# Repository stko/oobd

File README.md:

# OOBD - The Open Onboard Diagnostics Toolkit

OOBD (Open On Board Diagnostics) is a collection of open Source software and hardware for OBD Vehicle Diagnostics. Our target is to provide a flexible platform to do the most diagnostic tasks quick, handy and reliable. To do so, we've developed a whole set of applications, hardware and tools - and we still continue..

# Quickstart

To download, install, setup and run the software, please follow the instructions for [Android](http://oobd.org/doku.php?id=doc:startup_android) or [Windows](http://oobd.org/doku.php?id=doc:startup_windows).

For all documents, please use the links [Sitemap](http://oobd.org/doku.php?id=start&do=index) and [Manual](http://oobd.org/doku.php?id=doc:start) provided in the header of each page.

# Features
As the feature list became to long for the main page, we moved it to the separate [Feature](http://oobd.org/doku.php?id=web:features) page.

# Hardware

Although the build plans are available in the OOBD repository, we do recommend to better buy a finished CAN invader device at our partner [JATRA](http://caninvader.com/). It was found that there's a lot of experience and time needed to collect all parts and to solder the dongle by yourself. Especially for commercial applications it's more effective to directly order the complete units.

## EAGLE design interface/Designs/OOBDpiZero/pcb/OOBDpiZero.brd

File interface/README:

The OOBD firmware directory structure

The OOBD firmware has several hardware realisations (Designs), but always a common software core. To handle them all in one repository,
they are seperated into different Design Folders

`-- Designs
    |-- CORTEX
    |   `-- STM32F103E_Eclipse_GCC
    |       `-- D2
    `-- POSIX
        `-- GCC
            `-- D3

first sorted by the microcontroller platform, then by its particular controller itself and finally by the hardware design (Dxx), on which
that controller is used on.

The designs contains both the hardware description files (Schematics, PCB, etc) and also the software abstraction layers,
which connects the abstract functions to the real hardware and do also all the low level data handling like e.g.  the CAN -Bus

To make it simple, these designs just get a different number. Actual we have:

D1: the first, never realized protoype with an Atmel controller
D2: DXM hardware, optional combined with our own bus switching unit
D3: A pure simulator environment, emulating FreeRTOS and OOBD firmware as normal Unix pogramm. paired with a virtual serial port and a CAN-Bus
    simulator, written in python

The OOBD firmware core is hardware independend and so not bounded to the design folders.

It can be found in the OOBD folder, followed by a version folder for later extensions

`-- OOBD
    `-- v1

Finally the OS itself (we are using FreeRTOS) has is own indepenting directory structure, alligned to the standard structure of the FreeRTOS project.

`-- OS
    `-- FreeRTOSV6.1.0
        |-- Demo
        |   |-- Common
        |-- License
        `-- Source
            |-- include
            `-- portable

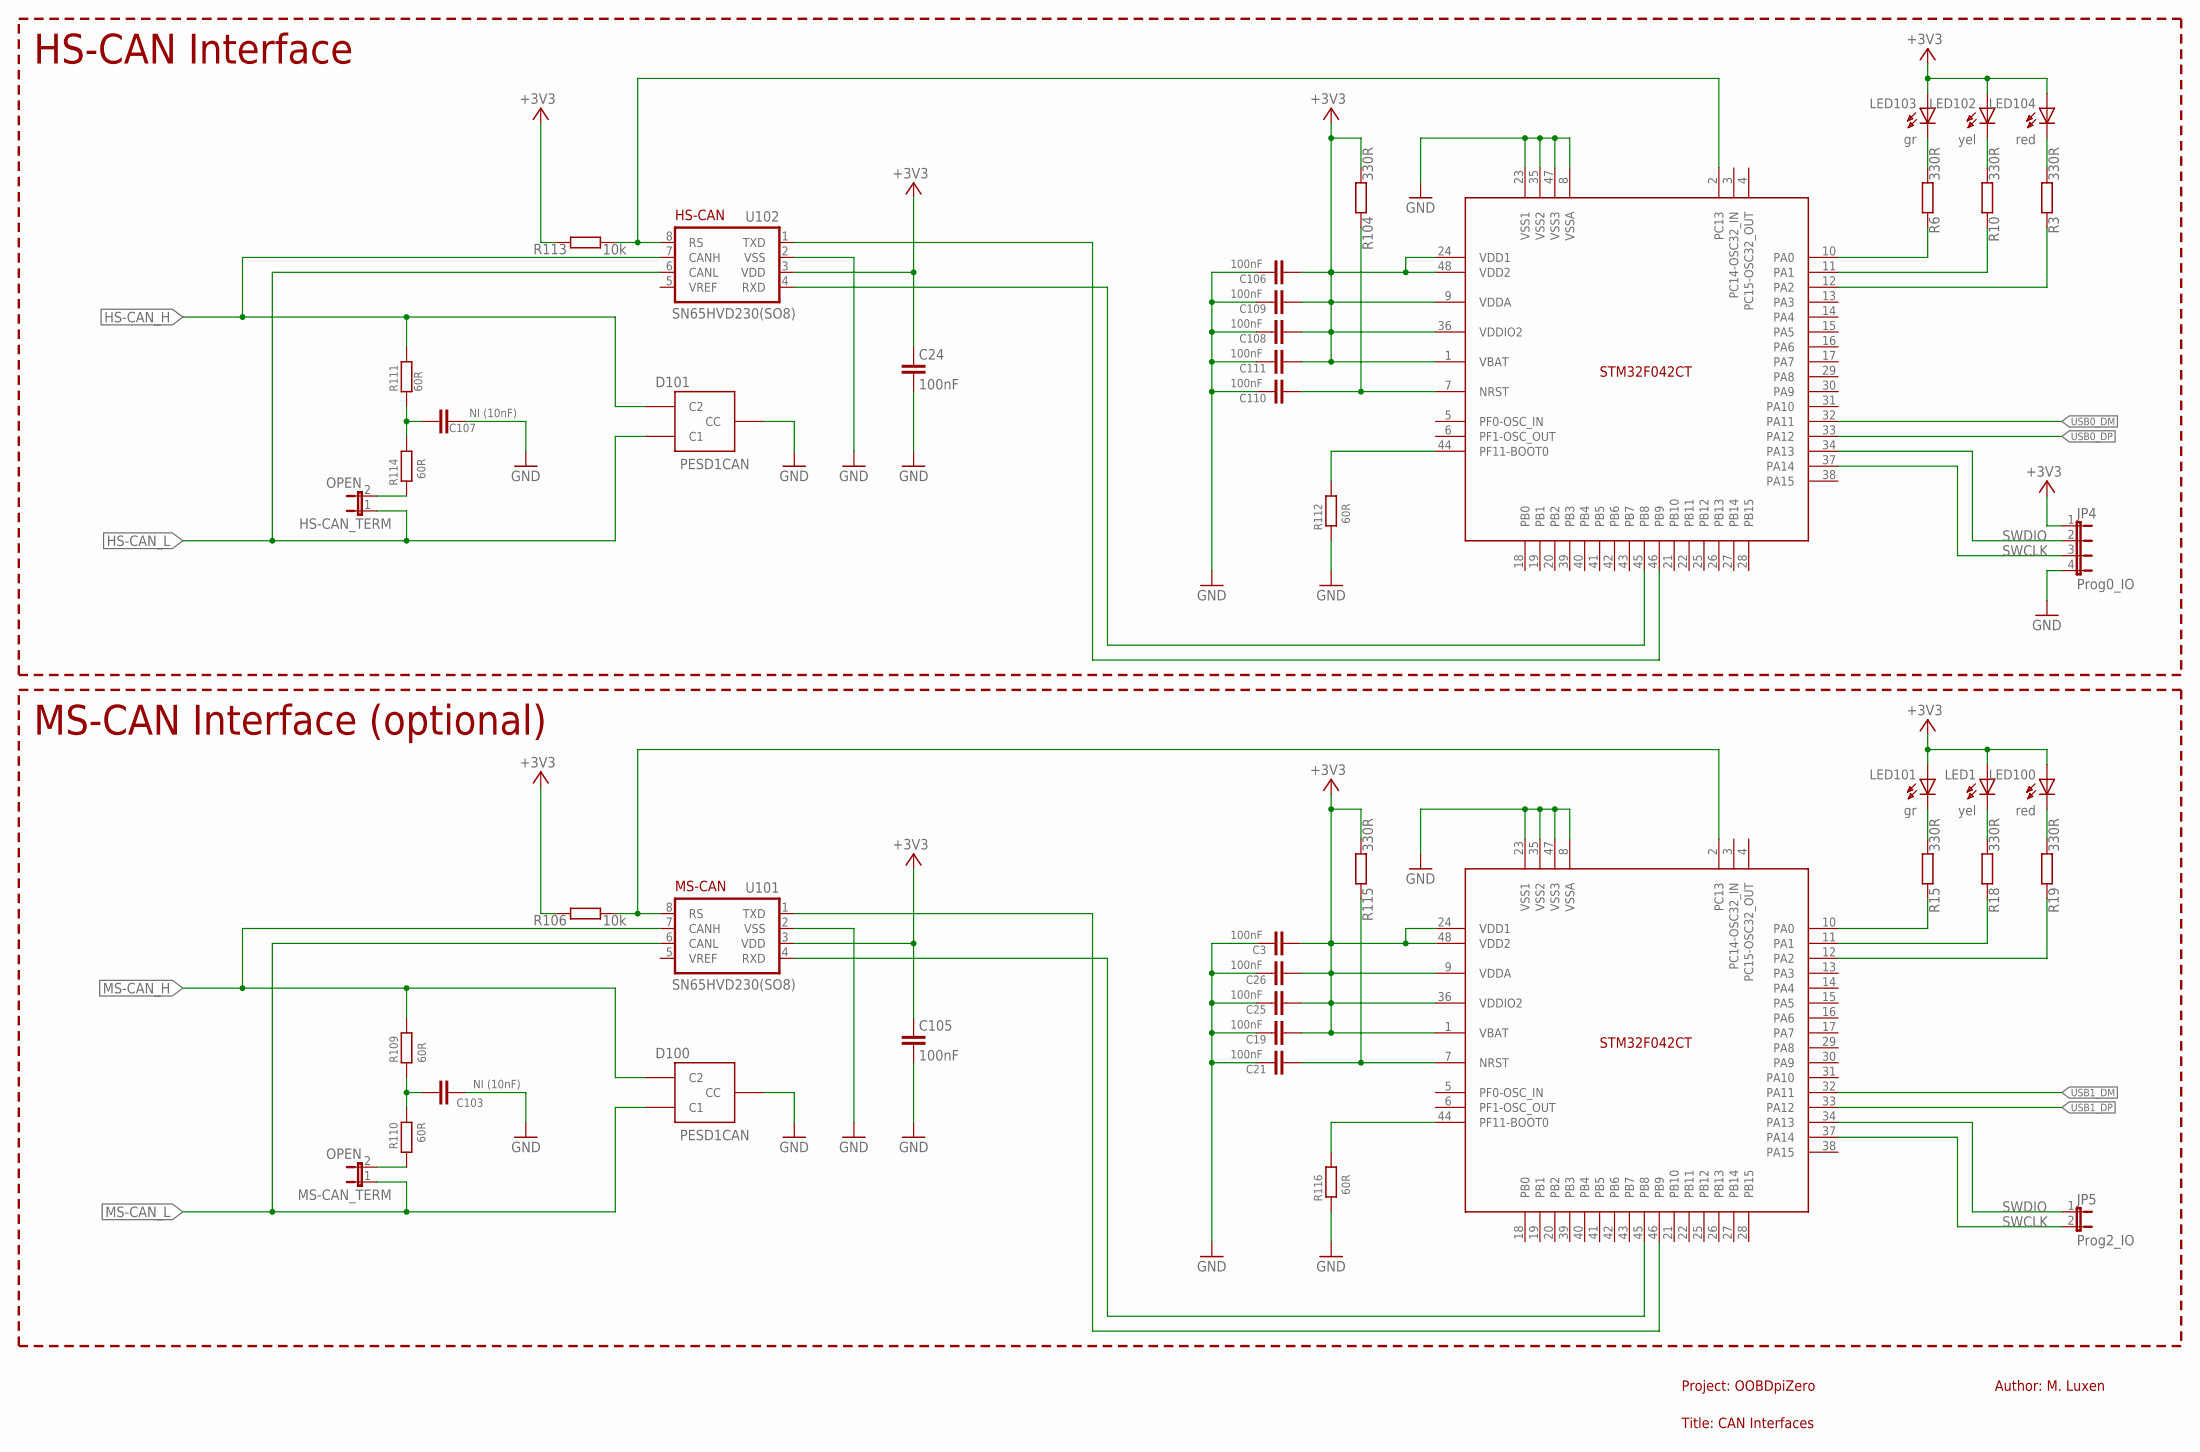
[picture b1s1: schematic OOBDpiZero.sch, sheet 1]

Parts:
C3, C19, C21, C25, C26, C106, C108, C109, C110, C111: 100nF; C0603
C24, C105: 100nF; C0603K
C103, C107: NI (10nF); C0603
D100, D101: PESD1CAN; SOT23
HS-CAN_TERM: OPEN; 1X02
JP4: Prog0_IO; JP4
JP5: Prog2_IO; JP1
LED1, LED102: yel; LED_0603
LED100, LED104: red; LED_0603
LED101, LED103: gr; LED_0603
MS-CAN_TERM: OPEN; 1X02
R3, R6, R10, R15, R18, R19, R104, R115: 330R; R0603
R106, R113: 10k; R0603
R109, R110, R111, R112, R114, R116: 60R; R0603
U101, U102: SN65HVD230(SO8); SO-08
U$100, U$102: STM32F042CT; LQFP48

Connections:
+3V3: C3.2, C19.2, C24.1, C25.2, C26.2, C105.1, C106.2, C108.2, C109.2, C111.2, JP4.1, LED1.A, LED100.A, LED101.A, LED102.A, LED103.A, LED104.A, R104.1, R106.2, R113.2, R115.1, U101.3 (VDD), U102.3 (VDD), U$100.1 (VBAT), U$100.9 (VDDA), U$100.24 (VDD1), U$100.36 (VDDIO2), U$100.48 (VDD2), U$102.1 (VBAT), U$102.9 (VDDA), U$102.24 (VDD1), U$102.36 (VDDIO2), U$102.48 (VDD2); also elsewhere on the board
GND: C3.1, C19.1, C21.1, C24.2, C25.1, C26.1, C103.2, C105.2, C106.1, C107.2, C108.1, C109.1, C110.1, C111.1, D100.3 (CC), D101.3 (CC), JP4.4, R112.2, R116.2, U101.2 (VSS), U102.2 (VSS), U$100.8 (VSSA), U$100.23 (VSS1), U$100.35 (VSS2), U$100.47 (VSS3), U$102.8 (VSSA), U$102.23 (VSS1), U$102.35 (VSS2), U$102.47 (VSS3); also elsewhere on the board
HS-CAN_H: D101.2 (C2), R111.2, U102.7 (CANH); also elsewhere on the board
HS-CAN_L: D101.1 (C1), HS-CAN_TERM.1, U102.6 (CANL); also elsewhere on the board
HS-CAN_RXD: U102.4 (RXD), U$100.45 (PB8)
HS-CAN_TXD: U102.1 (TXD), U$100.46 (PB9)
MS-CAN_H: D100.2 (C2), R109.2, U101.7 (CANH); also elsewhere on the board
MS-CAN_L: D100.1 (C1), MS-CAN_TERM.1, U101.6 (CANL); also elsewhere on the board
MS-CAN_RXD: U101.4 (RXD), U$102.45 (PB8)
MS-CAN_TXD: U101.1 (TXD), U$102.46 (PB9)
unnamed: C107.1, R111.1, R114.1
unnamed: R113.1, U102.8 (RS), U$100.2 (PC13)
unnamed: C103.1, R109.1, R110.1
unnamed: R6.2, U$100.10 (PA0)
unnamed: R10.2, U$100.11 (PA1)
unnamed: R112.1, U$100.44 (PF11-BOOT0)
unnamed: R3.2, U$100.12 (PA2)
unnamed: LED104.C, R3.1
unnamed: LED102.C, R10.1
unnamed: LED103.C, R6.1
unnamed: C110.2, R104.2, U$100.7 (NRST)
unnamed: R116.1, U$102.44 (PF11-BOOT0)
unnamed: R15.2, U$102.10 (PA0)
unnamed: R18.2, U$102.11 (PA1)
unnamed: R19.2, U$102.12 (PA2)
unnamed: LED100.C, R19.1
unnamed: LED1.C, R18.1
unnamed: LED101.C, R15.1
unnamed: C21.2, R115.2, U$102.7 (NRST)
unnamed: HS-CAN_TERM.2, R114.2
unnamed: MS-CAN_TERM.2, R110.2
unnamed: R106.1, U101.8 (RS), U$102.2 (PC13)
SWCLK: JP4.3, JP5.2, U$100.37 (PA14), U$102.37 (PA14)
SWDIO: JP4.2, JP5.1, U$100.34 (PA13), U$102.34 (PA13)
USB0_DM: U$100.32 (PA11); also elsewhere on the board
USB0_DP: U$100.33 (PA12); also elsewhere on the board
USB1_DM: U$102.32 (PA11); also elsewhere on the board
USB1_DP: U$102.33 (PA12); also elsewhere on the board

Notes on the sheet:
HS-CAN Interface
Project: OOBDpiZero
Title: CAN Interfaces
HS-CAN
MS-CAN Interface (optional)
MS-CAN
Author: M. Luxen

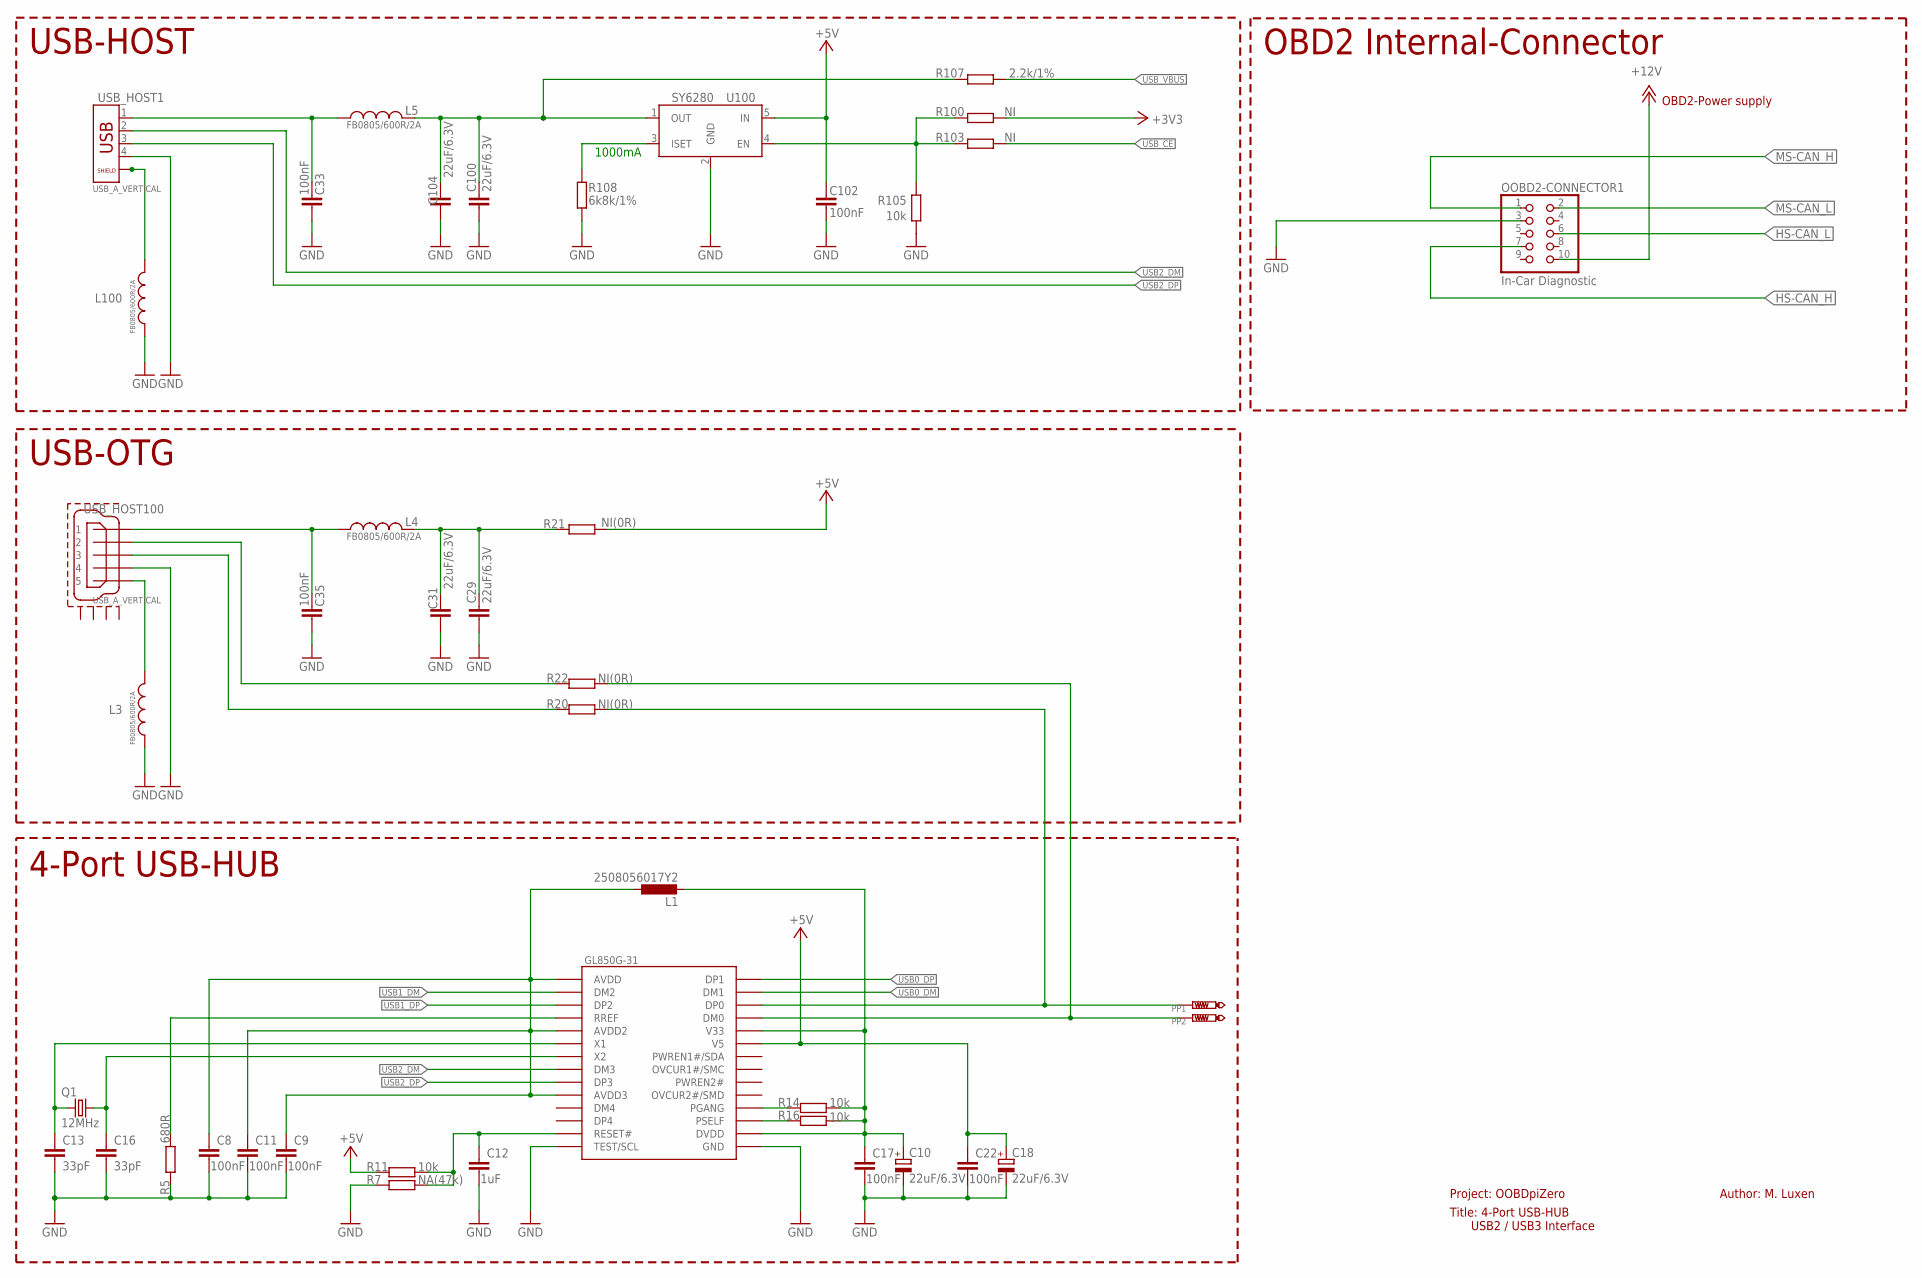
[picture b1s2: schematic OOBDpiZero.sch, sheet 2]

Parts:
C8, C9, C11, C17, C22: 100nF; C0603
C10, C18: 22uF/6.3V; SMC_A
C12: 1uF; C0603
C13, C16: 33pF; C0603
C29, C31, C100, C104: 22uF/6.3V; C0603
C33, C35, C102: 100nF; C0603K
L1: 2508056017Y2; L0805@1
L3, L4, L5, L100: FB0805/600R/2A; L0603
OOBD2-CONNECTOR1: In-Car Diagnostic; 2X05/90
PP1, PP2: PTR1PAD1-11; P1-11
Q1: 12MHz; SM49
R5: 680R; R0603
R7: NA(47k); R0603
R11, R14, R16, R105: 10k; R0603
R20, R22: NI(0R); R0603
R21: NI(0R); R0805
R100, R103: NI; R0603
R107: 2.2k/1%; R0603
R108: 6k8k/1%; R0603
U100: SY6280; SOT23-5
U$101: GL850G-31; TSSOP28
USB_HOST1: USB_A_VERTICAL; USB_PN87520_DEV_PTH
USB_HOST100: USB_A_VERTICAL; 47589-0001

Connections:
+3V3: R100.2; also elsewhere on the board
+5V: C18.+, C22.1, C102.1, R11.1, R21.2, U100.5 (IN), U$101.23 (V5); also elsewhere on the board
+12V: OOBD2-CONNECTOR1.10; also elsewhere on the board
GND: C8.2, C9.2, C10.-, C11.2, C12.2, C13.2, C16.2, C17.2, C18.-, C22.2, C29.2, C31.2, C33.2, C35.2, C100.2, C102.2, C104.2, L3.1, L100.1, OOBD2-CONNECTOR1.3, R5.1, R7.1, R105.1, R108.1, U100.2 (GND), U$101.14 (TEST/SCL), U$101.15 (GND), USB_HOST1.4, USB_HOST100.4; also elsewhere on the board
HS-CAN_H: OOBD2-CONNECTOR1.7; also elsewhere on the board
HS-CAN_L: OOBD2-CONNECTOR1.6; also elsewhere on the board
MS-CAN_H: OOBD2-CONNECTOR1.1; also elsewhere on the board
MS-CAN_L: OOBD2-CONNECTOR1.2; also elsewhere on the board
unnamed: C29.1, C31.1, L4.1, R21.1
unnamed: C16.1, Q1.2, U$101.7 (X2)
unnamed: C13.1, Q1.1, U$101.6 (X1)
unnamed: C10.+, C17.1, L1.2, R14.2, R16.2, U$101.16 (DVDD), U$101.24 (V33)
unnamed: R14.1, U$101.18 (PGANG)
unnamed: R16.1, U$101.17 (PSELF)
unnamed: C12.1, R7.2, R11.2, U$101.13 (RESET#)
unnamed: R22.1, USB_HOST100.2
unnamed: C8.1, C9.1, C11.1, L1.1, U$101.1 (AVDD), U$101.5 (AVDD2), U$101.10 (AVDD3)
unnamed: R5.2, U$101.4 (RREF)
unnamed: C33.1, L5.2, USB_HOST1.1
unnamed: L100.2, USB_HOST1.P$1 (5), USB_HOST1.P$2 (6)
unnamed: R20.1, USB_HOST100.3
unnamed: L3.2, USB_HOST100.5
unnamed: R108.2, U100.3 (ISET)
unnamed: C100.1, C104.1, L5.1, R107.2, U100.1 (OUT)
unnamed: C35.1, L4.2, USB_HOST100.1
PP22: PP1.P$1, R20.2, U$101.26 (DP0)
PP23: PP2.P$1, R22.2, U$101.25 (DM0)
USB0_DM: U$101.27 (DM1); also elsewhere on the board
USB0_DP: U$101.28 (DP1); also elsewhere on the board
USB1_DM: U$101.2 (DM2); also elsewhere on the board
USB1_DP: U$101.3 (DP2); also elsewhere on the board
USB1_EN: R100.1, R103.1, R105.2, U100.4 (EN)
USB2_DM: U$101.8 (DM3), USB_HOST1.2
USB2_DP: U$101.9 (DP3), USB_HOST1.3
USB_CE: R103.2; also elsewhere on the board
USB_VBUS: R107.1; also elsewhere on the board

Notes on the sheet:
USB-HOST
1000mA
USB-OTG
4-Port USB-HUB
Project: OOBDpiZero
Title: 4-Port USB-HUB USB2 / USB3 Interface
Author: M. Luxen
OBD2-Power supply
OBD2 Internal-Connector

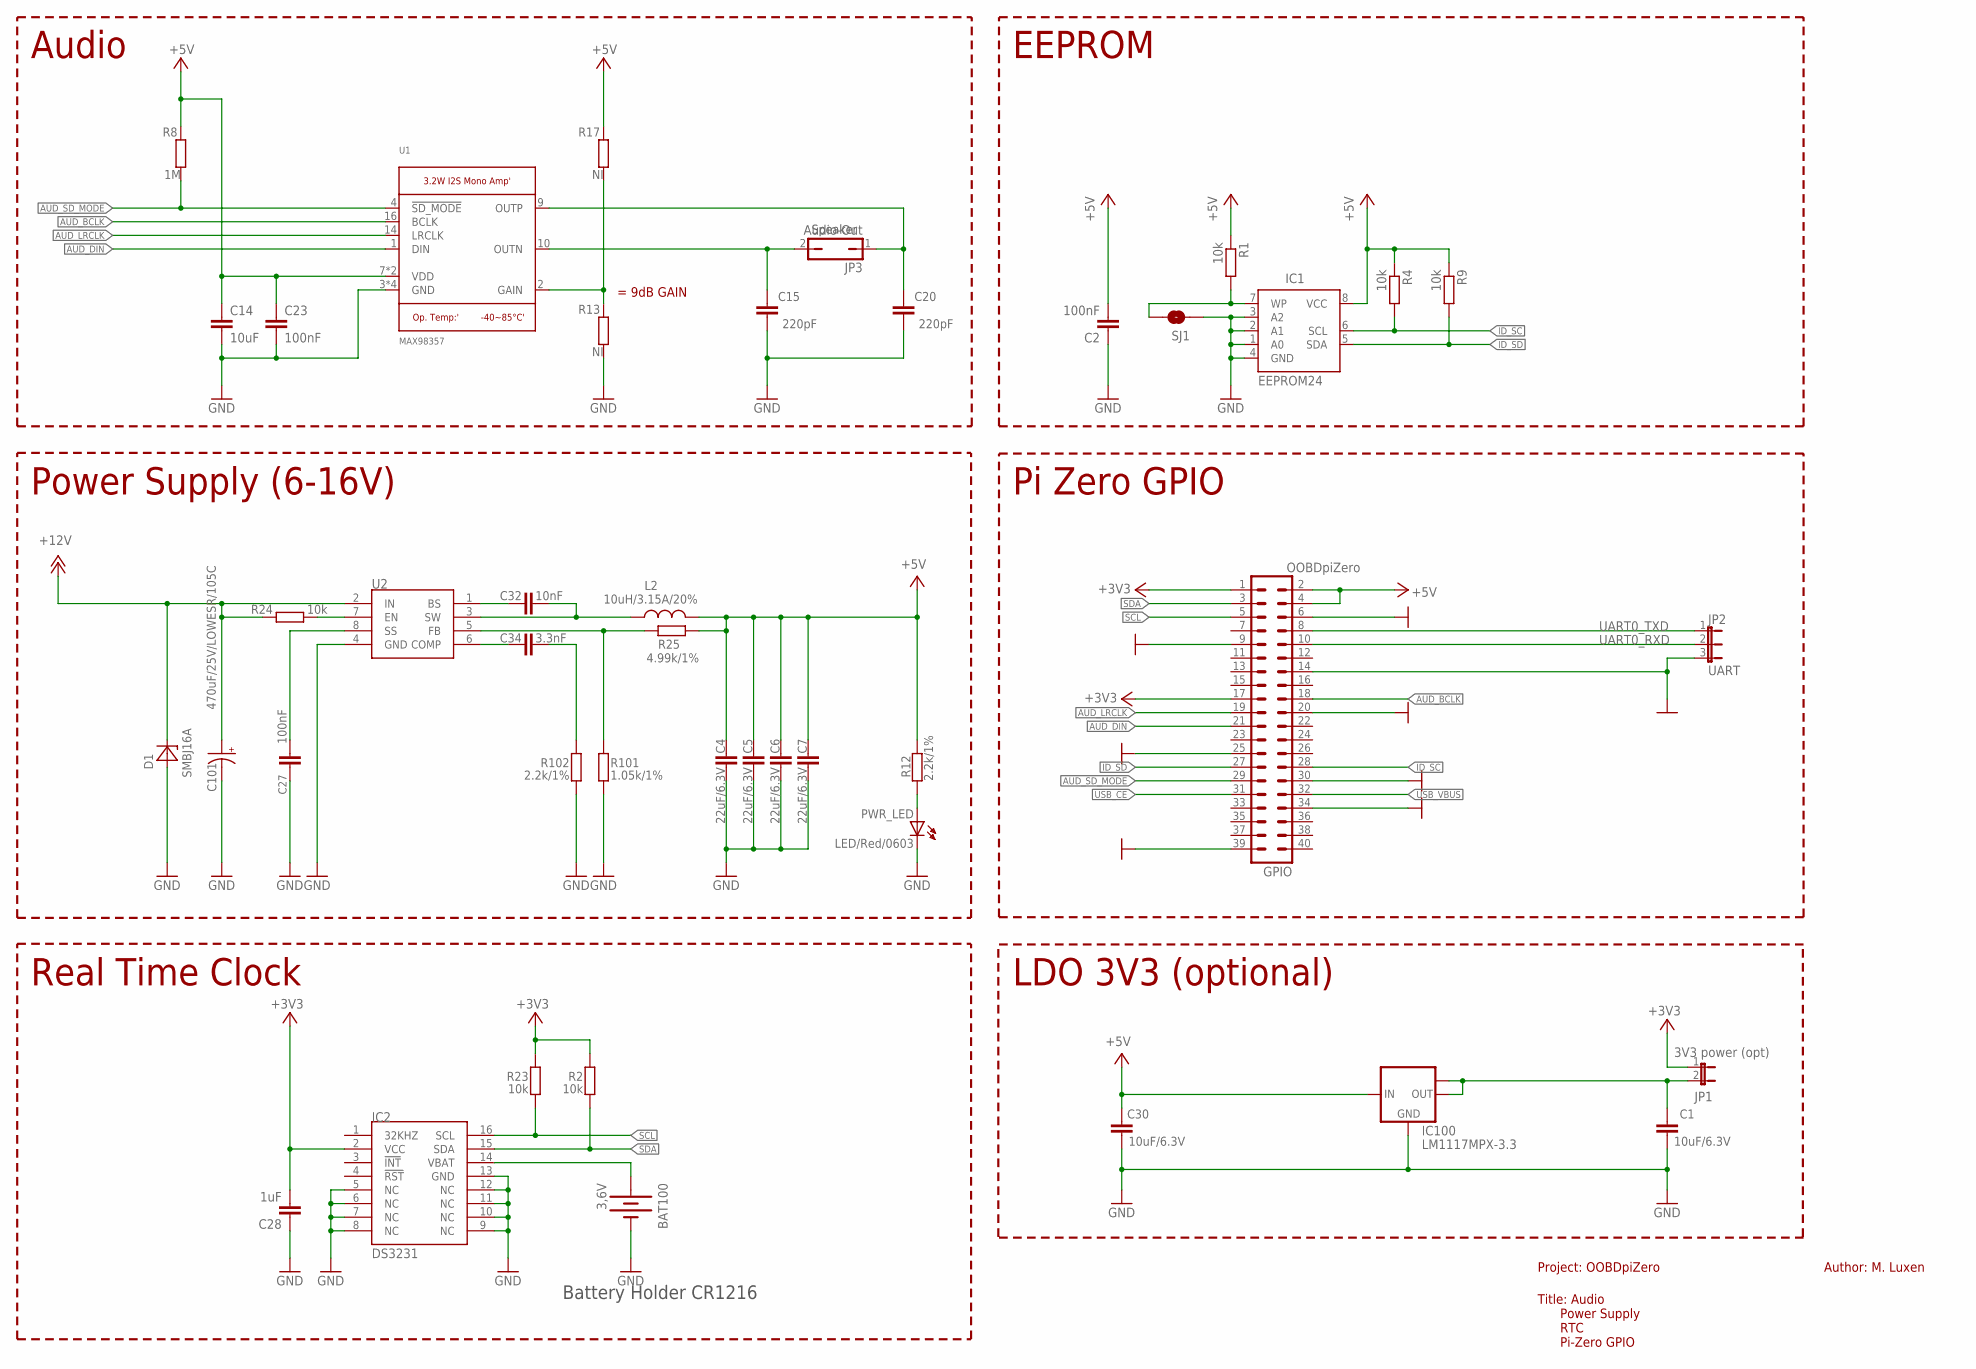
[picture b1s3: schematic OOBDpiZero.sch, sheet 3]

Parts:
BAT100: 3,6V; BATTCON_12MM_PTH
C1, C30: 10uF/6.3V; C0603
C2, C27: 100nF; C0603
C4, C5, C6, C7: 22uF/6.3V; C0603
C14: 10uF; C0805K
C15, C20: 220pF; C0603K
C23: 100nF; C0603K
C28: 1uF; C0603
C32: 10nF; C0603
C34: 3.3nF; C0603
C101: 470uF/25V/LOWESR/105C; PANASONIC_D
D1: SMBJ16A; DO214AA
GPIO: OOBDpiZero; PIZERO_THOUGH_HOLE
IC1: EEPROM24; SOIC8
IC2: DS3231; SOIC-16W
IC100: LM1117MPX-3.3; SOT223
JP1: 3V3 power (opt); JP1
JP2: UART; JP2
JP3: Audio-Out; JP1
L2: 10uH/3.15A/20%; 8X8MM_3131
PWR_LED: LED/Red/0603; LED-0603
R1, R2, R4, R9, R23, R24: 10k; R0603
R8: 1M; R0603
R12, R102: 2.2k/1%; R0603
R13, R17: NI; R0603
R25: 4.99k/1%; R0603
R101: 1.05k/1%; R0603
SJ1: SOLDERJUMPERTRACE; SJ_2S-TRACE
U1: MAX98357; QFN16_3MM
U2: MP1482; SOIC8

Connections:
+3V3: C28.2, GPIO.1, GPIO.17, IC2.2 (VCC), JP1.1, R2.1, R23.1; also elsewhere on the board
+5V: C2.2, C4.1, C5.1, C6.1, C7.1, C14.1, C23.1, C30.1, GPIO.2, GPIO.4, IC1.8 (VCC), IC100.3 (IN), L2.2, R1.1, R4.1, R8.2, R9.1, R12.1, R17.2, R25.2, U1.7 (VDD), U1.8 (VDD); also elsewhere on the board
+12V: C101.+, D1.C, R24.1, U2.2 (IN); also elsewhere on the board
AUD_BCLK: GPIO.18, U1.16 (BCLK)
AUD_DIN: GPIO.21, U1.1 (DIN)
AUD_LRCLK: GPIO.19, U1.14 (LRCLK)
AUD_SD_MODE: GPIO.29, R8.1, U1.4 (!SD_MODE)
GND: BAT100.GND (-), C1.2, C2.1, C4.2, C5.2, C6.2, C7.2, C14.2, C15.1, C20.1, C23.2, C27.2, C28.1, C30.2, C101.-, D1.A, GPIO.6, GPIO.9, GPIO.14, GPIO.20, GPIO.25, GPIO.30, GPIO.34, GPIO.39, IC1.1 (A0), IC1.2 (A1), IC1.3 (A2), IC1.4 (GND), IC2.5 (NC), IC2.6 (NC), IC2.7 (NC), IC2.8 (NC), IC2.9 (NC), IC2.10 (NC), IC2.11 (NC), IC2.12 (NC), IC2.13 (GND), IC100.1 (GND), JP2.3, PWR_LED.C, R13.1, R101.2, R102.2, SJ1.1, U1.3 (GND), U1.11 (GND), U1.15 (GND), U1.THERMAL (GND), U2.4 (GND); also elsewhere on the board
ID_SC: GPIO.28, IC1.6 (SCL), R4.2
ID_SD: GPIO.27, IC1.5 (SDA), R9.2
unnamed: C15.2, JP3.2, U1.10 (OUTN)
unnamed: C27.1, U2.8 (SS)
unnamed: R24.2, U2.7 (EN)
unnamed: C32.1, U2.1 (BS)
unnamed: C32.2, L2.1, U2.3 (SW)
unnamed: C34.1, U2.6 (COMP)
unnamed: C34.2, R102.1
unnamed: C20.2, JP3.1, U1.9 (OUTP)
unnamed: R13.2, R17.1, U1.2 (GAIN)
unnamed: IC1.7 (WP), R1.2, SJ1.2
unnamed: C1.1, IC100.2 (OUT), IC100.TAB (OUT1), JP1.2
unnamed: R25.1, R101.1, U2.5 (FB)
unnamed: PWR_LED.A, R12.2
SCL: GPIO.5, IC2.16 (SCL), R23.2
SDA: GPIO.3, IC2.15 (SDA), R2.2
UART0_RXD: GPIO.10, JP2.2
UART0_TXD: GPIO.8, JP2.1
USB_CE: GPIO.31; also elsewhere on the board
USB_VBUS: GPIO.32; also elsewhere on the board
VBAT: BAT100.VCC@1 (+), IC2.14 (VBAT)

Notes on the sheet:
Power Supply (6-16V)
Author: M. Luxen
Project: OOBDpiZero
Title: Audio Power Supply RTC Pi-Zero GPIO
Real Time Clock
Battery Holder CR1216
Pi Zero GPIO
Audio
Speaker
EEPROM
LDO 3V3 (optional)
= 9dB GAIN

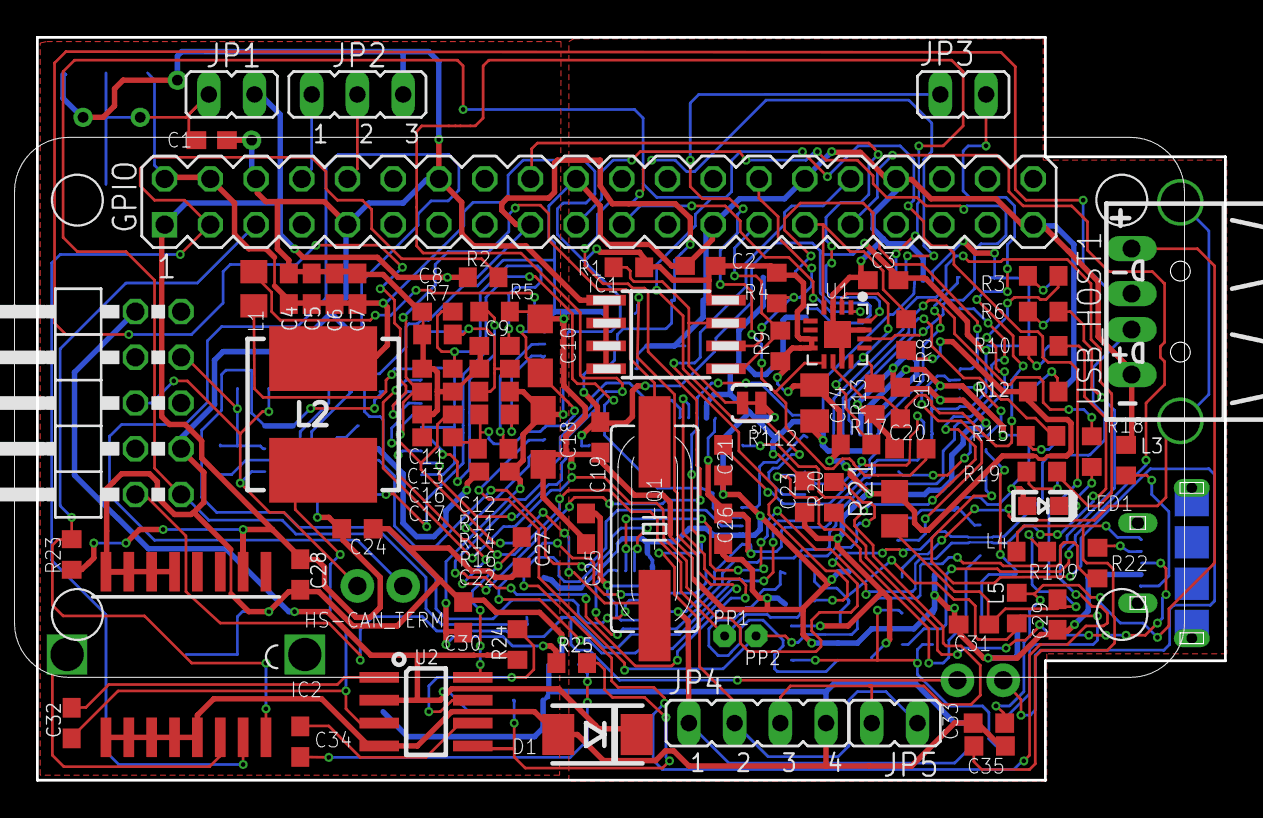
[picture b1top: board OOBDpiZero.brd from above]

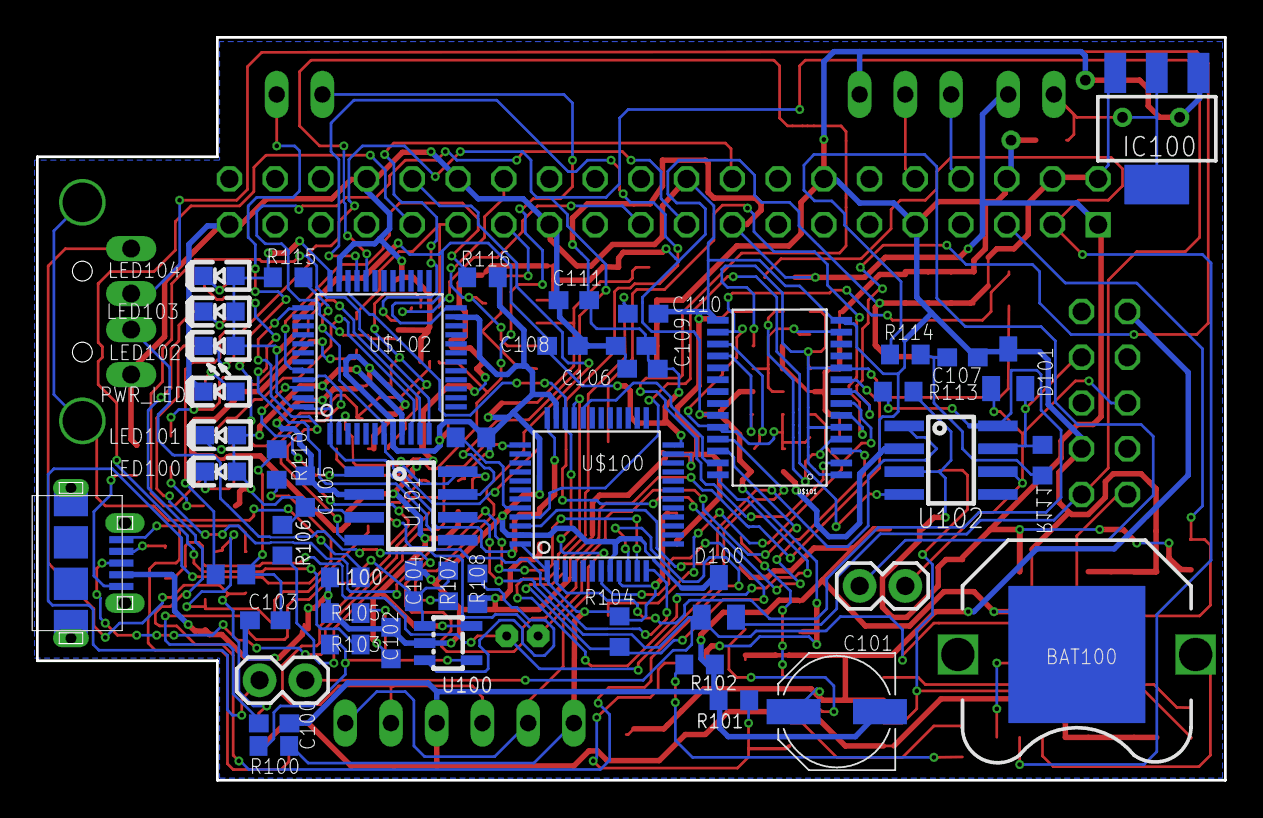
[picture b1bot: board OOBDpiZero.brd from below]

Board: 2 copper layers, 66.0 x 41.3 mm, 132 parts (49 on the bottom side), 88 nets.

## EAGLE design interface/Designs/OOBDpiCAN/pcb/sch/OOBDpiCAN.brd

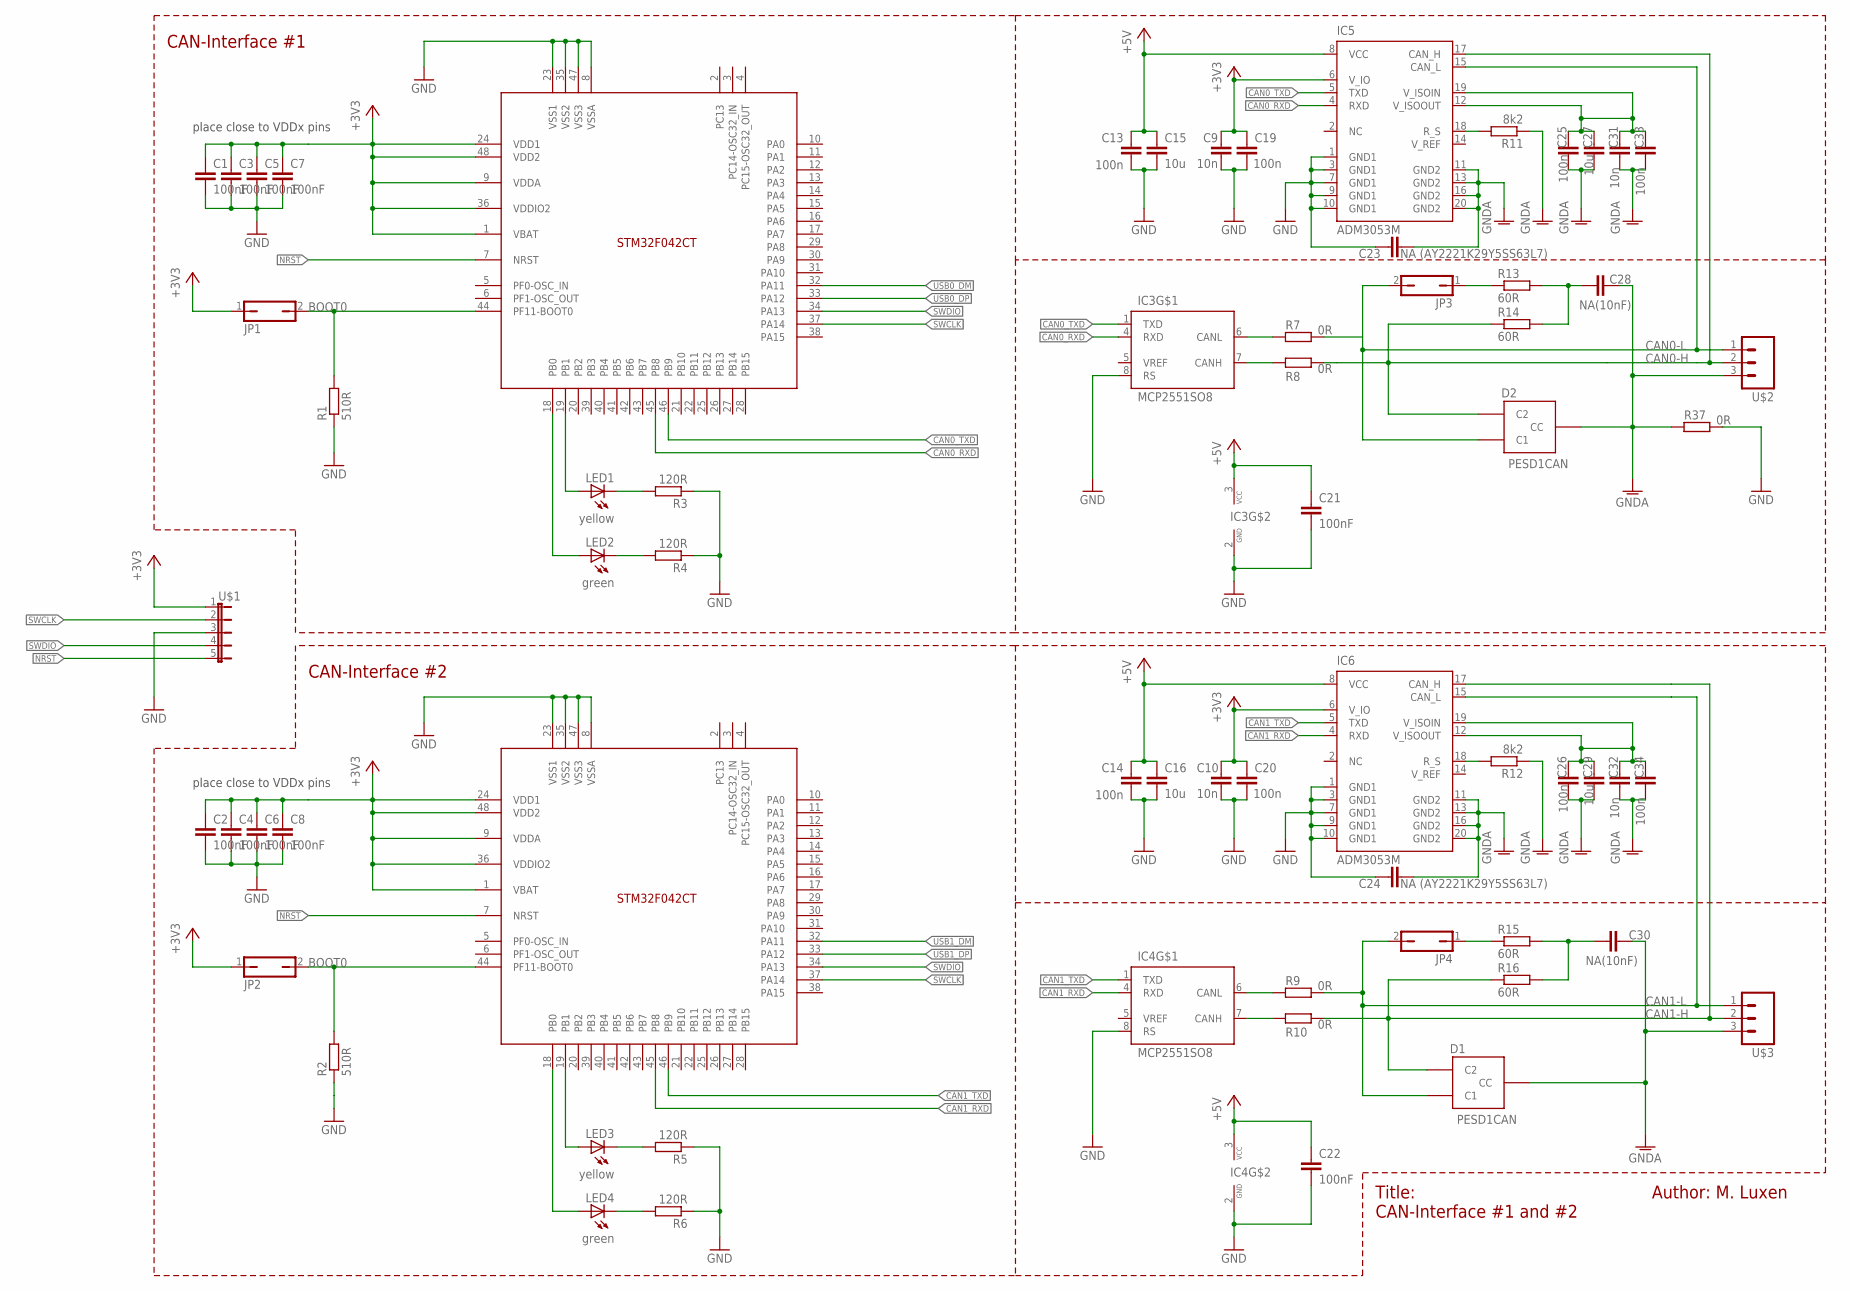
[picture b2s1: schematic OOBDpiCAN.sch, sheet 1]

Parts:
C1, C2, C3, C4, C5, C6, C7, C8, C21, C22: 100nF; C0603
C9, C10: 10n; C0603K
C13, C14, C19, C20: 100n; C0603K
C15, C16, C27, C29: 10u; C0805K
C23, C24: NA (AY2221K29Y5SS63L7); C075-032X103
C25, C26, C33, C34: 100n; C0805K
C28, C30: NA(10nF); C0603
C31, C32: 10n; C0805K
D1, D2: PESD1CAN; SOT23
IC1, IC2: STM32F042CT; LQFP48
IC3, IC4: MCP2551SO8; SO08
IC5, IC6: ADM3053M; SO20W
JP1, JP2, JP3, JP4: JP1Q; JP1
LED1, LED3: yellow; CHIPLED_0805
LED2, LED4: green; CHIPLED_0805
R1, R2: 510R; R0603
R3, R4, R5, R6: 120R; R0603
R7, R8, R9, R10, R37: 0R; 0207/10
R11, R12: 8k2; R0603
R13, R14, R15, R16: 60R; R0603
U$1: JP5E; JP5
U$2, U$3: M03; SCREWTERMINAL-3.5MM-3

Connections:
+3V3: C1.1, C2.1, C3.1, C4.1, C5.1, C6.1, C7.1, C8.1, C9.1, C10.1, C19.1, C20.1, IC1.1 (VBAT), IC1.9 (VDDA), IC1.24 (VDD1), IC1.36 (VDDIO2), IC1.48 (VDD2), IC2.1 (VBAT), IC2.9 (VDDA), IC2.24 (VDD1), IC2.36 (VDDIO2), IC2.48 (VDD2), IC5.6 (V_IO), IC6.6 (V_IO), JP1.1, JP2.1, U$1.1; also elsewhere on the board
+5V: C13.1, C14.1, C15.1, C16.1, C21.1, C22.1, IC3.3 (VCC), IC4.3 (VCC), IC5.8 (VCC), IC6.8 (VCC); also elsewhere on the board
BOOT0: IC1.44 (PF11-BOOT0), IC2.44 (PF11-BOOT0), JP1.2, JP2.2, R1.2, R2.2; also elsewhere on the board
CAN0-H: D2.2 (C2), IC5.17 (CAN_H), R8.2, R14.1, U$2.2 (3)
CAN0-L: D2.1 (C1), IC5.15 (CAN_L), JP3.2, R7.2, U$2.1 (2)
CAN0_RXD: IC1.45 (PB8), IC3.4 (RXD), IC5.4 (RXD)
CAN0_TXD: IC1.46 (PB9), IC3.1 (TXD), IC5.5 (TXD)
CAN1-H: D1.2 (C2), IC6.17 (CAN_H), R10.2, R16.1, U$3.2 (3)
CAN1-L: D1.1 (C1), IC6.15 (CAN_L), JP4.2, R9.2, U$3.1 (2)
CAN1_RXD: IC2.45 (PB8), IC4.4 (RXD), IC6.4 (RXD)
CAN1_TXD: IC2.46 (PB9), IC4.1 (TXD), IC6.5 (TXD)
GND: C1.2, C2.2, C3.2, C4.2, C5.2, C6.2, C7.2, C8.2, C9.2, C10.2, C13.2, C14.2, C15.2, C16.2, C19.2, C20.2, C21.2, C22.2, C23.1, C24.1, IC1.8 (VSSA), IC1.23 (VSS1), IC1.35 (VSS2), IC1.47 (VSS3), IC2.8 (VSSA), IC2.23 (VSS1), IC2.35 (VSS2), IC2.47 (VSS3), IC3.2 (GND), IC3.8 (RS), IC4.2 (GND), IC4.8 (RS), IC5.1 (GND1), IC5.3 (GND1), IC5.7 (GND1), IC5.9 (GND1), IC5.10 (GND1), IC6.1 (GND1), IC6.3 (GND1), IC6.7 (GND1), IC6.9 (GND1), IC6.10 (GND1), R1.1, R2.1, R3.1, R4.1, R5.1, R6.1, R37.2, U$1.3; also elsewhere on the board
GNDA: C23.2, C24.2, C25.2, C26.2, C27.2, C28.2, C29.2, C30.2, C31.2, C32.2, C33.2, C34.2, D1.3 (CC), D2.3 (CC), IC5.11 (GND2), IC5.13 (GND2), IC5.16 (GND2), IC5.20 (GND2), IC6.11 (GND2), IC6.13 (GND2), IC6.16 (GND2), IC6.20 (GND2), R11.1, R12.1, R37.1, U$2.3 (4), U$3.3 (4)
unnamed: IC5.18 (R_S), R11.2
unnamed: IC6.18 (R_S), R12.2
unnamed: C26.1, C29.1, C32.1, C34.1, IC6.12 (V_ISOOUT), IC6.19 (V_ISOIN)
unnamed: IC3.6 (CANL), R7.1
unnamed: IC3.7 (CANH), R8.1
unnamed: IC1.19 (PB1), LED1.A
unnamed: IC1.18 (PB0), LED2.A
unnamed: LED1.C, R3.2
unnamed: LED2.C, R4.2
unnamed: IC4.7 (CANH), R10.1
unnamed: IC4.6 (CANL), R9.1
unnamed: JP4.1, R15.1
unnamed: IC2.19 (PB1), LED3.A
unnamed: IC2.18 (PB0), LED4.A
unnamed: LED3.C, R5.2
unnamed: LED4.C, R6.2
unnamed: JP3.1, R13.1
unnamed: C30.1, R15.2, R16.2
unnamed: C28.1, R13.2, R14.2
unnamed: C25.1, C27.1, C31.1, C33.1, IC5.12 (V_ISOOUT), IC5.19 (V_ISOIN)
NRST: IC1.7 (NRST), IC2.7 (NRST), U$1.5; also elsewhere on the board
SWCLK: IC1.37 (PA14), IC2.37 (PA14), U$1.2; also elsewhere on the board
SWDIO: IC1.34 (PA13), IC2.34 (PA13), U$1.4; also elsewhere on the board
USB0_DM: IC1.32 (PA11); also elsewhere on the board
USB0_DP: IC1.33 (PA12); also elsewhere on the board
USB1_DM: IC2.32 (PA11); also elsewhere on the board
USB1_DP: IC2.33 (PA12); also elsewhere on the board

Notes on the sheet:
place close to VDDx pins
Author: M. Luxen
Title:
CAN-Interface #1 and #2
CAN-Interface #2
CAN-Interface #1

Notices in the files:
interface/D2/Firmware_FreeRTOS/Demo/CORTEX_STM32F103E_Eclipse_GCC/src/SystemConfig.c:
under the terms of the GNU General Public License (version 2) as published
parts and their libraries:
SparkFun: Licensing: CC v3.0 Share-Alike You are welcome to use this library for commercial purposes.
EagleLibrary_Wuerth_Elektronik _eiCan_Wi: Copyright: Würth Elektronik
SparkFun-Capacitors: Licensing: Creative Commons ShareAlike 4.0 International - https://creativecommons.org/licenses/by-sa/4.0
